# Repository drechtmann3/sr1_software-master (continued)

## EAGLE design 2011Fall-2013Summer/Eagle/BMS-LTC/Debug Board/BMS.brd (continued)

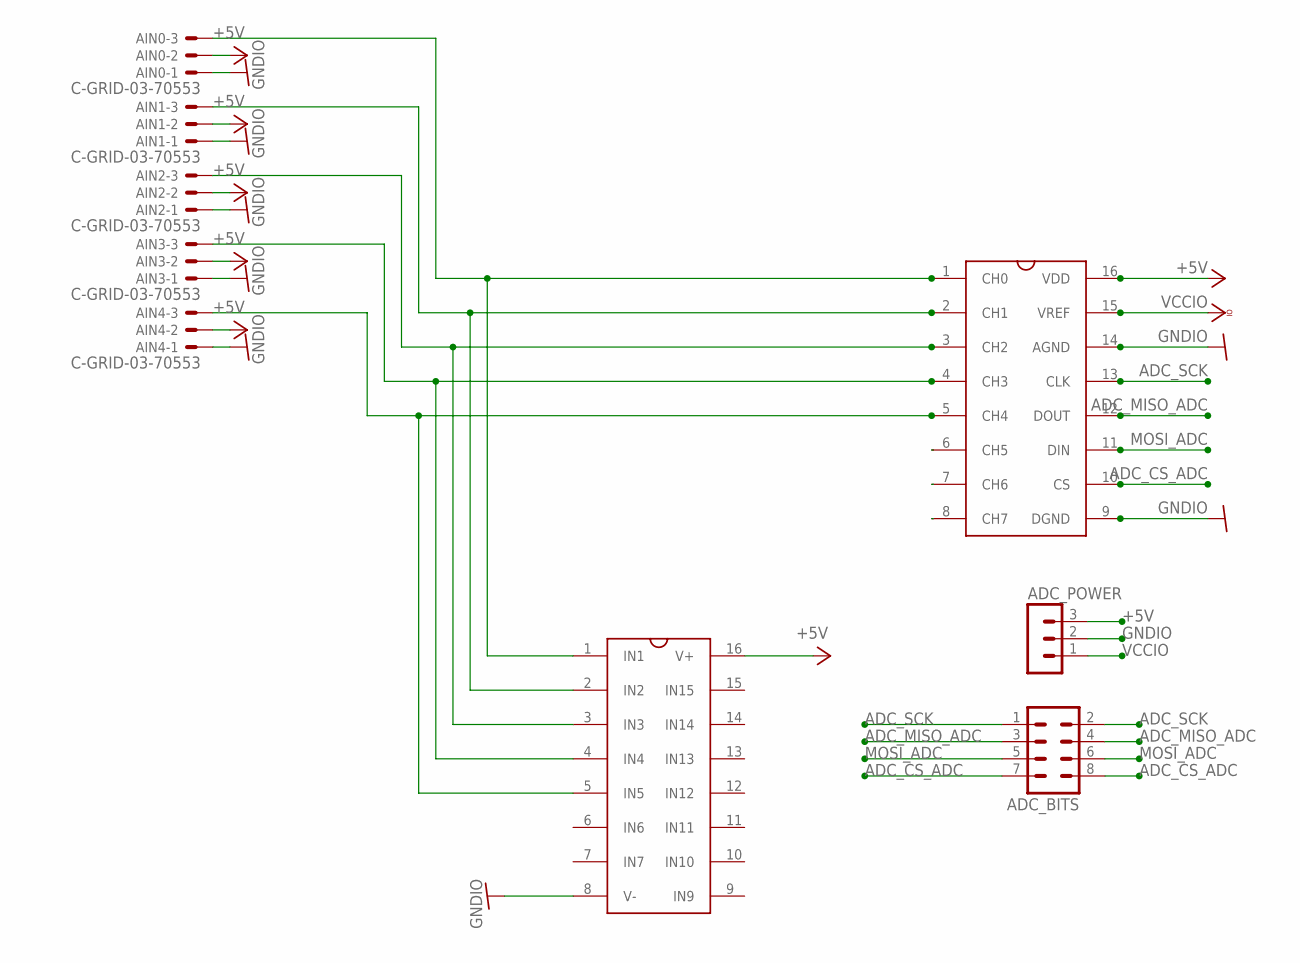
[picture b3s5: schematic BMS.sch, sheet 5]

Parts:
ADC_BITS: MA04-2
ADC_POWER: MA03-1
AIN0, AIN1, AIN2, AIN3, AIN4: C-GRID-03-70553; 70553-03
U$1: SP720APP; SO16
U$6: MCP-3008; SO16

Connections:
+5V: ADC_POWER.3, AIN0.2, AIN1.2, AIN2.2, AIN3.2, AIN4.2, U$1.16 (V+), U$6.16 (VDD); also elsewhere on the board
ADC_CS_ADC: ADC_BITS.7, ADC_BITS.8, U$6.10 (CS)
ADC_MISO_ADC: ADC_BITS.3, ADC_BITS.4, U$6.12 (DOUT)
ADC_SCK: ADC_BITS.1, ADC_BITS.2, U$6.13 (CLK)
GNDIO: ADC_POWER.2, AIN0.1, AIN1.1, AIN2.1, AIN3.1, AIN4.1, U$1.8 (V-), U$6.9 (DGND), U$6.14 (AGND); also elsewhere on the board
MOSI_ADC: ADC_BITS.5, ADC_BITS.6, U$6.11 (DIN)
unnamed: AIN0.3, U$1.1 (IN1), U$6.1 (CH0)
unnamed: AIN1.3, U$1.2 (IN2), U$6.2 (CH1)
unnamed: AIN2.3, U$1.3 (IN3), U$6.3 (CH2)
unnamed: AIN3.3, U$1.4 (IN4), U$6.4 (CH3)
unnamed: AIN4.3, U$1.5 (IN5), U$6.5 (CH4)
VCCIO: ADC_POWER.1, U$6.15 (VREF); also elsewhere on the board

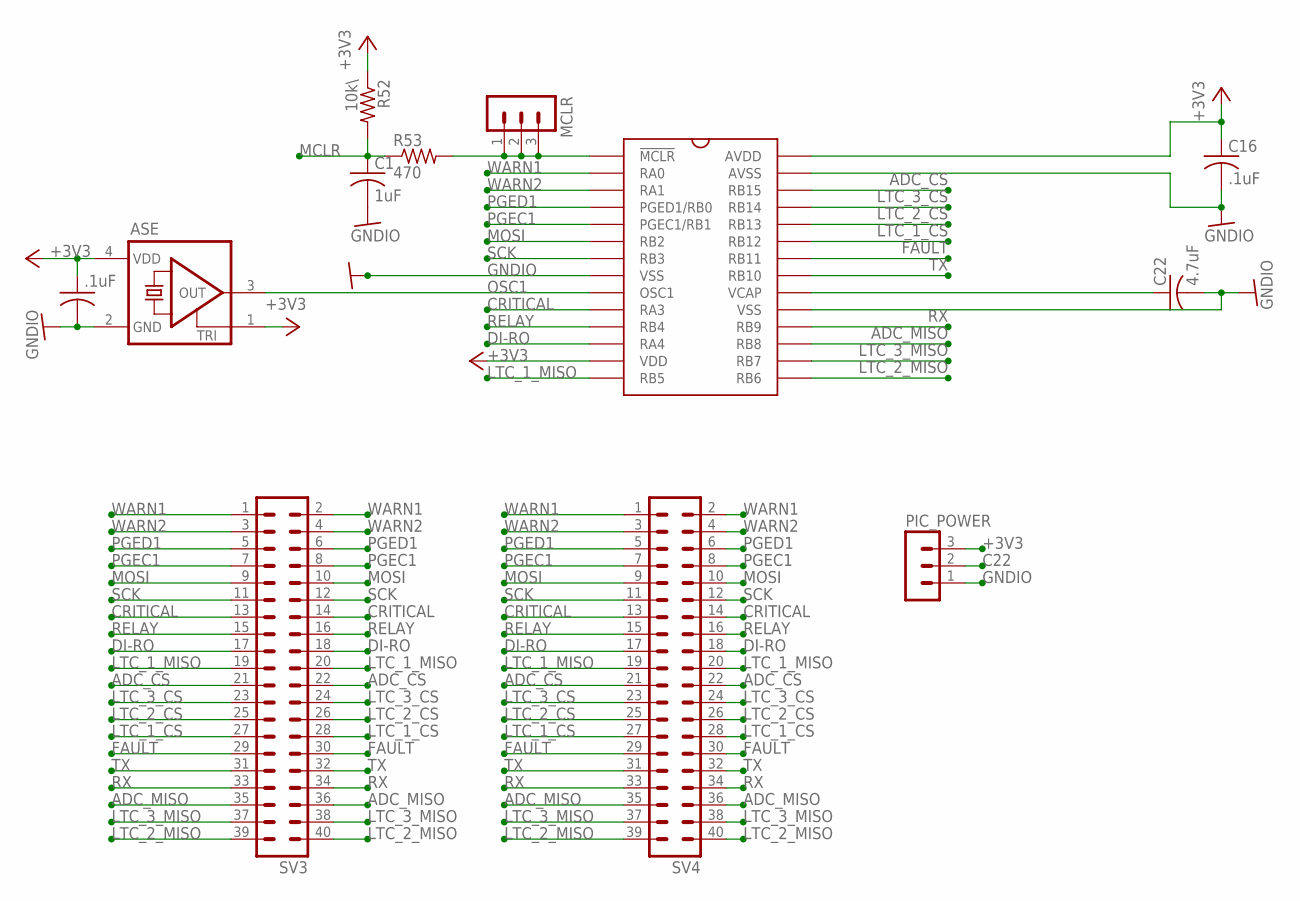
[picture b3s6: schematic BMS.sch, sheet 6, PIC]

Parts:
C1: 1uF; C1206
C16, C48: .1uF; C1206
C22: 4.7uF; C1206
MCLR: MA03-1
PIC_POWER: MA03-1
R52: 10k\; R1206
R53: 470; R1206
SV3, SV4: MA20-2
U$2: PIC24HJ128GP-202; SO28W
U$3: ASE

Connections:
+3V3: C16.1, C48.1, PIC_POWER.3, R52.1, U$2.13 (VDD), U$2.28 (AVDD), U$3.1 (TRI), U$3.4 (VDD); also elsewhere on the board
ADC_CS: SV3.21, SV3.22, SV4.21, SV4.22, U$2.26 (RB15)
ADC_MISO: SV3.35, SV3.36, SV4.35, SV4.36, U$2.17 (RB8)
C22: C22.1, PIC_POWER.2, U$2.20 (VCAP)
CRITICAL: SV3.13, SV3.14, SV4.13, SV4.14, U$2.10 (RA3)
DI-RO: SV3.17, SV3.18, SV4.17, SV4.18, U$2.12 (RA4)
FAULT: SV3.29, SV3.30, SV4.29, SV4.30, U$2.22 (RB11)
GNDIO: C1.2, C16.2, C22.2, C48.2, PIC_POWER.1, U$2.8 (VSS), U$2.19 (VSS), U$2.27 (AVSS), U$3.2 (GND); also elsewhere on the board
LTC_1_CS: SV3.27, SV3.28, SV4.27, SV4.28, U$2.23 (RB12)
LTC_1_MISO: SV3.19, SV3.20, SV4.19, SV4.20, U$2.14 (RB5)
LTC_2_CS: SV3.25, SV3.26, SV4.25, SV4.26, U$2.24 (RB13)
LTC_2_MISO: SV3.39, SV3.40, SV4.39, SV4.40, U$2.15 (RB6)
LTC_3_CS: SV3.23, SV3.24, SV4.23, SV4.24, U$2.25 (RB14)
LTC_3_MISO: SV3.37, SV3.38, SV4.37, SV4.38, U$2.16 (RB7)
MCLR: C1.1, R52.2, R53.1; also elsewhere on the board
MOSI: SV3.9, SV3.10, SV4.9, SV4.10, U$2.6 (RB2)
unnamed: MCLR.1, MCLR.2, MCLR.3, R53.2, U$2.1 (!MCLR!)
OSC1: U$2.9 (OSC1), U$3.3 (OUT); also elsewhere on the board
PGEC1: SV3.7, SV3.8, SV4.7, SV4.8, U$2.5 (PGEC1/RB1); also elsewhere on the board
PGED1: SV3.5, SV3.6, SV4.5, SV4.6, U$2.4 (PGED1/RB0); also elsewhere on the board
RELAY: SV3.15, SV3.16, SV4.15, SV4.16, U$2.11 (RB4)
RX: SV3.33, SV3.34, SV4.33, SV4.34, U$2.18 (RB9)
SCK: SV3.11, SV3.12, SV4.11, SV4.12, U$2.7 (RB3)
TX: SV3.31, SV3.32, SV4.31, SV4.32, U$2.21 (RB10)
WARN1: SV3.1, SV3.2, SV4.1, SV4.2, U$2.2 (RA0)
WARN2: SV3.3, SV3.4, SV4.3, SV4.4, U$2.3 (RA1)

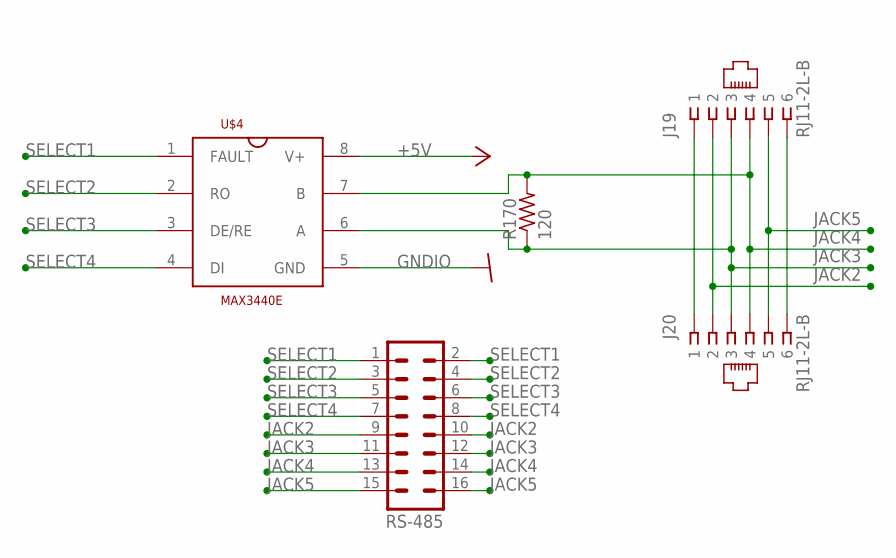
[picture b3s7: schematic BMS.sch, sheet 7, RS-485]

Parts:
J19, J20: RJ11-2L-B; RJ11-NO_SHIELD
R170: 120; R1206
RS-485: MA08-2
U$4: MAX3440E; SO-08

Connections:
+5V: U$4.8 (V+); also elsewhere on the board
GNDIO: U$4.5 (GND); also elsewhere on the board
JACK2: J19.2, J20.2, RS-485.9, RS-485.10
JACK3: J19.3, J20.3, R170.1, RS-485.11, RS-485.12, U$4.6 (A)
JACK4: J19.4, J20.4, R170.2, RS-485.13, RS-485.14, U$4.7 (B)
JACK5: J19.5, J20.5, RS-485.15, RS-485.16
unnamed: J19.1, J20.1
unnamed: J19.6, J20.6
SELECT1: RS-485.1, RS-485.2, U$4.1 (FAULT)
SELECT2: RS-485.3, RS-485.4, U$4.2 (RO)
SELECT3: RS-485.5, RS-485.6, U$4.3 (DE/RE)
SELECT4: RS-485.7, RS-485.8, U$4.4 (DI)

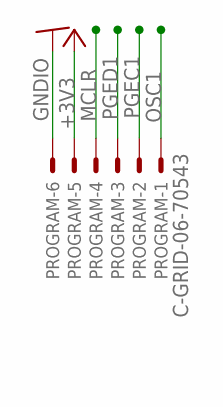
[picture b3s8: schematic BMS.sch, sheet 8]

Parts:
PROGRAM: C-GRID-06-70543; 70543-06

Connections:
+3V3: PROGRAM.5; also elsewhere on the board
GNDIO: PROGRAM.6; also elsewhere on the board
MCLR: PROGRAM.4; also elsewhere on the board
OSC1: PROGRAM.1; also elsewhere on the board
PGEC1: PROGRAM.2; also elsewhere on the board
PGED1: PROGRAM.3; also elsewhere on the board

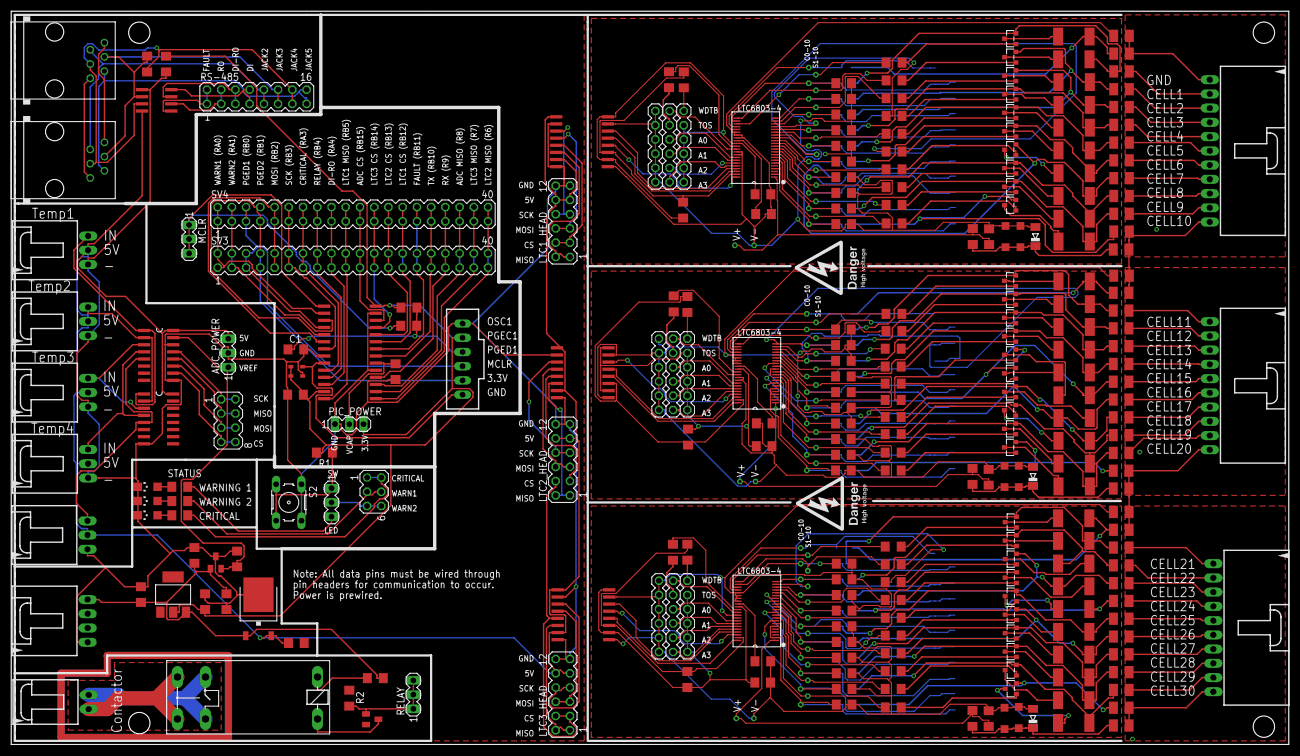
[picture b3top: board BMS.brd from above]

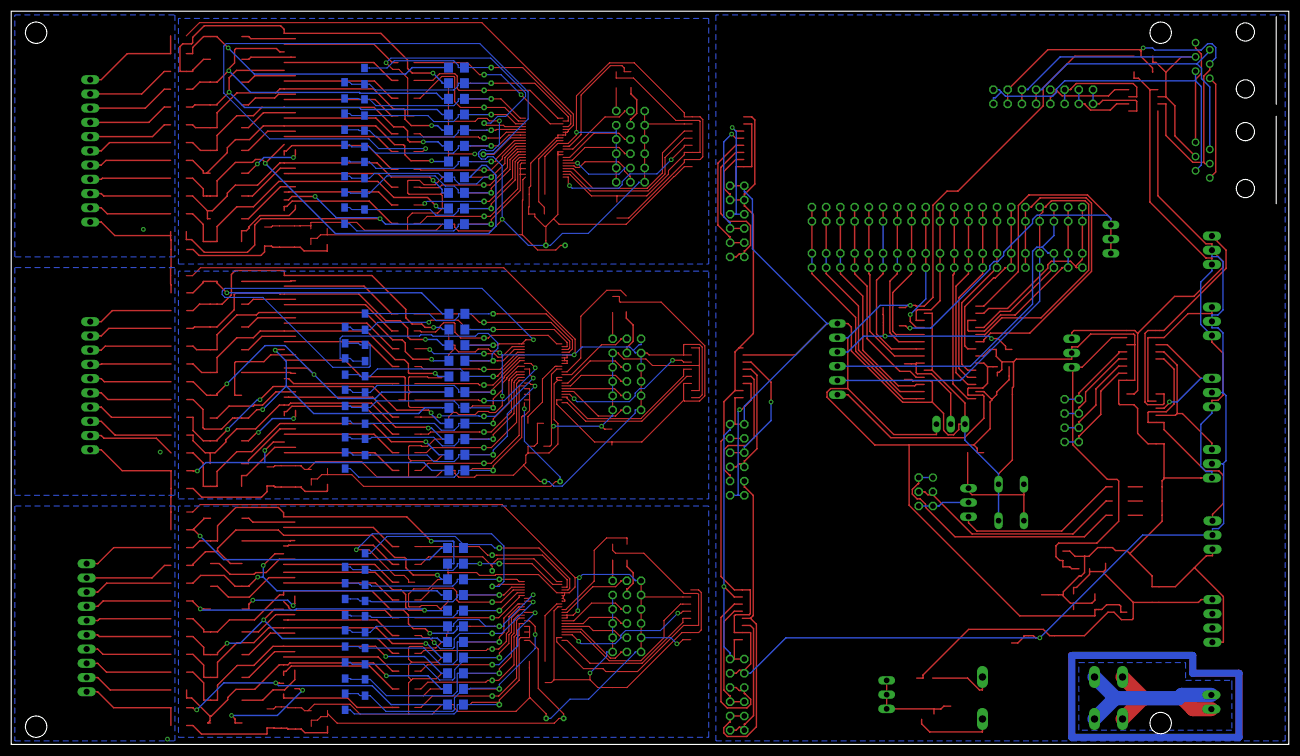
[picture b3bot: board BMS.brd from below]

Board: 2 copper layers, 228.0 x 130.8 mm, 389 parts (84 on the bottom side), 311 nets.

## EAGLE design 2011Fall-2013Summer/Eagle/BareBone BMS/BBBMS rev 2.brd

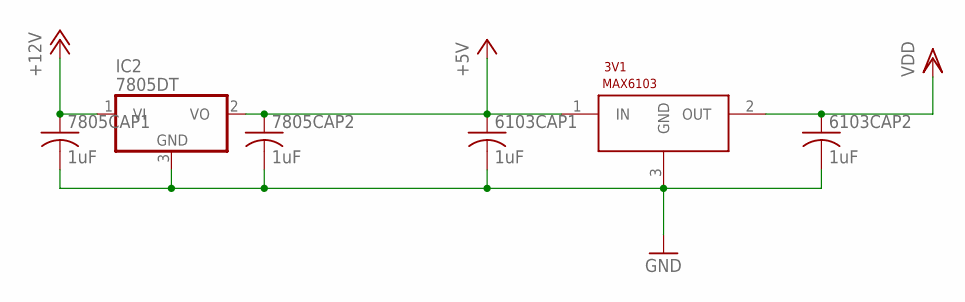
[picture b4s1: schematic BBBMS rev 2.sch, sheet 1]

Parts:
3V1: MAX6103; SOT23
6103CAP1, 6103CAP2, 7805CAP1, 7805CAP2: 1uF; C1206
IC2: 7805DT; TO252

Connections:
5V: 3V1.1 (IN), 6103CAP1.1, 7805CAP2.1, IC2.2 (VO); also elsewhere on the board
12V: 7805CAP1.1, IC2.1 (VI); also elsewhere on the board
GND: 3V1.3 (GND), 6103CAP1.2, 6103CAP2.2, 7805CAP1.2, 7805CAP2.2, IC2.3 (GND); also elsewhere on the board
VREF: 3V1.2 (OUT), 6103CAP2.1; also elsewhere on the board

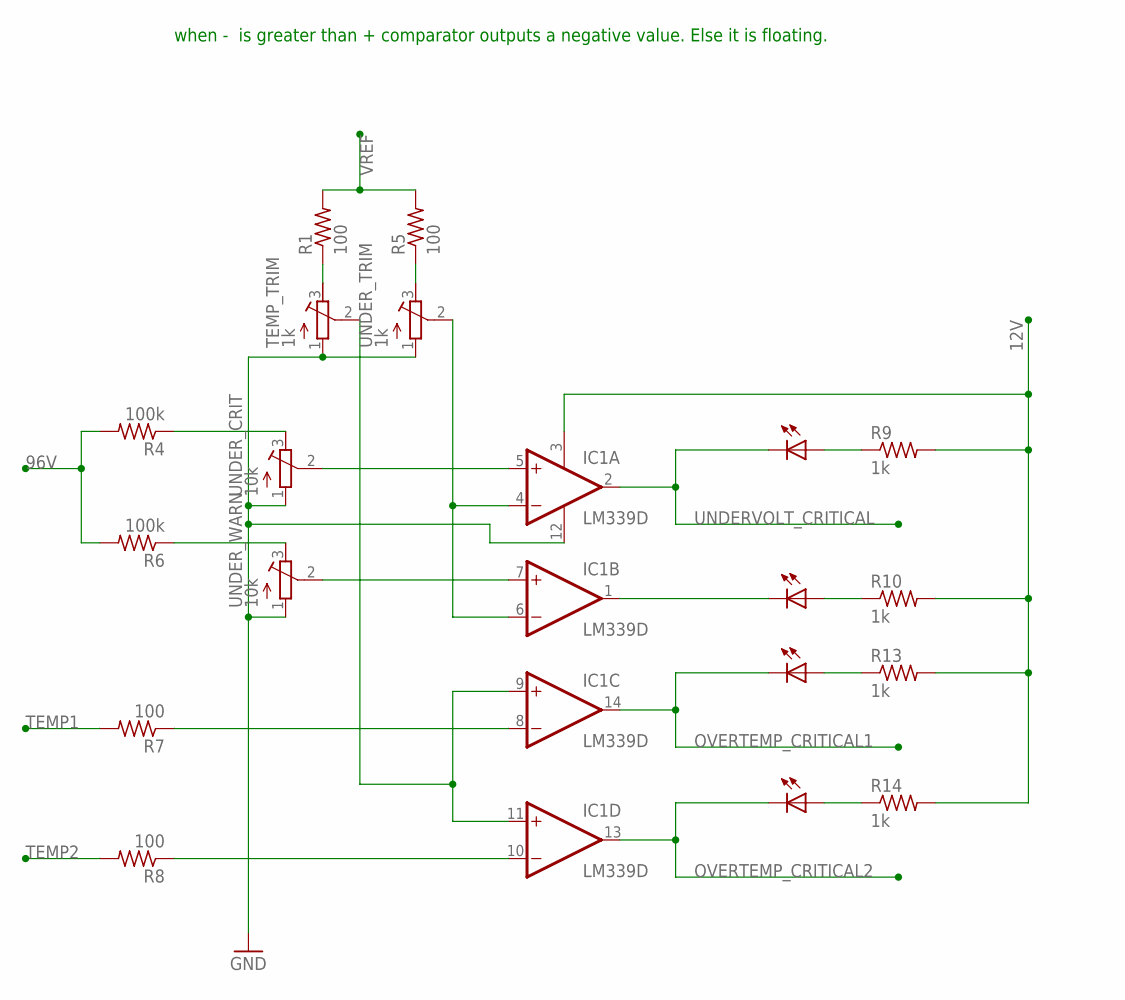
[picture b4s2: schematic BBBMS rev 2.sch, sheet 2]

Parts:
IC1: LM339D; SO14
OVERTEMP1, OVERTEMP2: LEDCHIPLED_1206; CHIPLED_1206
R1, R5, R7, R8: 100; R1206
R4, R6: 100k; R1206
R9, R10, R13, R14: 1k; R1206
TEMP_TRIM: 1k; RTRIMTS63Y
UNDERVOLT: LEDCHIPLED_1206; CHIPLED_1206
UNDERVOLT_WARN: LEDCHIPLED_1206; CHIPLED_1206
UNDER_CRIT: 10k; RTRIMTS63Y
UNDER_TRIM: 1k; RTRIMTS63Y
UNDER_WARN: 10k; RTRIMTS63Y

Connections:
12V: IC1.3 (V+), R9.2, R10.2, R13.2, R14.2; also elsewhere on the board
96V: R4.2, R6.2; also elsewhere on the board
GND: IC1.12 (GND), TEMP_TRIM.1 (A), UNDER_CRIT.1 (A), UNDER_TRIM.1 (A), UNDER_WARN.1 (A); also elsewhere on the board
unnamed: IC1.8 (-IN), R7.1
unnamed: IC1.7 (+IN), UNDER_WARN.2 (S)
unnamed: IC1.5 (+IN), UNDER_CRIT.2 (S)
unnamed: IC1.9 (+IN), IC1.11 (+IN), TEMP_TRIM.2 (S)
unnamed: R6.1, UNDER_WARN.3 (E)
unnamed: IC1.10 (-IN), R8.1
unnamed: R4.1, UNDER_CRIT.3 (E)
unnamed: IC1.4 (-IN), IC1.6 (-IN), UNDER_TRIM.2 (S)
unnamed: R5.1, UNDER_TRIM.3 (E)
unnamed: R1.1, TEMP_TRIM.3 (E)
unnamed: R9.1, UNDERVOLT.A
unnamed: R10.1, UNDERVOLT_WARN.A
unnamed: OVERTEMP1.A, R13.1
unnamed: OVERTEMP2.A, R14.1
OVERTEMP_CRITICAL1: IC1.14 (OUT), OVERTEMP1.C; also elsewhere on the board
OVERTEMP_CRITICAL2: IC1.13 (OUT), OVERTEMP2.C; also elsewhere on the board
TEMP1: R7.2; also elsewhere on the board
TEMP2: R8.2; also elsewhere on the board
UNDERVOLT_CRITICAL: IC1.2 (OUT), UNDERVOLT.C; also elsewhere on the board
UNDERVOLT_WARNING: IC1.1 (OUT), UNDERVOLT_WARN.C
VREF: R1.2, R5.2; also elsewhere on the board

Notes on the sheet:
when - is greater than + comparator outputs a negative value. Else it is floating.

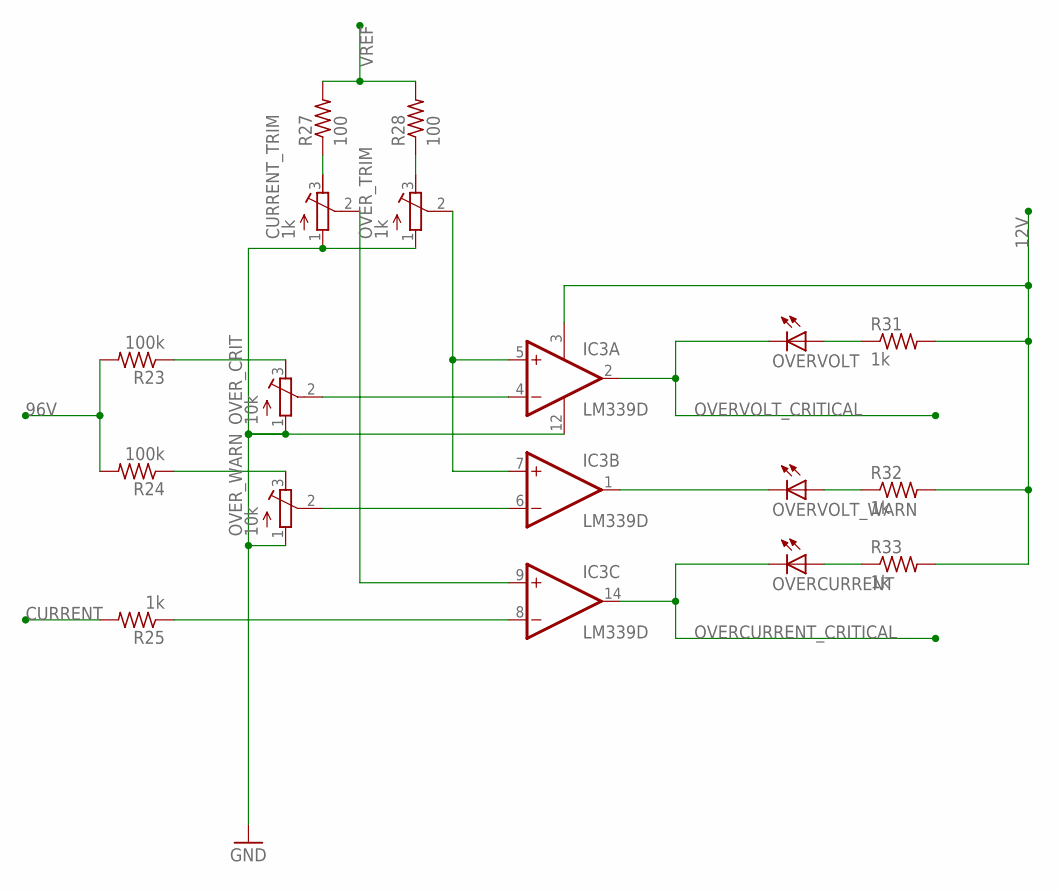
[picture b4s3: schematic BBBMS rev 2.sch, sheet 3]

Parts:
CURRENT_TRIM: 1k; RTRIMTS63Y
IC3: LM339D; SO14
OVERCURRENT: LEDCHIPLED_1206; CHIPLED_1206
OVERVOLT: LEDCHIPLED_1206; CHIPLED_1206
OVERVOLT_WARN: LEDCHIPLED_1206; CHIPLED_1206
OVER_CRIT: 10k; RTRIMTS63Y
OVER_TRIM: 1k; RTRIMTS63Y
OVER_WARN: 10k; RTRIMTS63Y
R23, R24: 100k; R1206
R25, R31, R32, R33: 1k; R1206
R27, R28: 100; R1206

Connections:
12V: IC3.3 (V+), R31.2, R32.2, R33.2; also elsewhere on the board
96V: R23.2, R24.2; also elsewhere on the board
CURRENT: R25.2; also elsewhere on the board
GND: CURRENT_TRIM.1 (A), IC3.12 (GND), OVER_CRIT.1 (A), OVER_TRIM.1 (A), OVER_WARN.1 (A); also elsewhere on the board
unnamed: IC3.6 (-IN), OVER_WARN.2 (S)
unnamed: IC3.4 (-IN), OVER_CRIT.2 (S)
unnamed: CURRENT_TRIM.2 (S), IC3.9 (+IN)
unnamed: OVER_CRIT.3 (E), R23.1
unnamed: OVER_WARN.3 (E), R24.1
unnamed: IC3.8 (-IN), R25.1
unnamed: IC3.5 (+IN), IC3.7 (+IN), OVER_TRIM.2 (S)
unnamed: OVER_TRIM.3 (E), R28.1
unnamed: CURRENT_TRIM.3 (E), R27.1
unnamed: OVERVOLT.A, R31.1
unnamed: OVERVOLT_WARN.A, R32.1
unnamed: OVERCURRENT.A, R33.1
OVERCURRENT_CRITICAL: IC3.14 (OUT), OVERCURRENT.C; also elsewhere on the board
OVERVOLT_CRITICAL: IC3.2 (OUT), OVERVOLT.C; also elsewhere on the board
OVERVOLT_WARNING1: IC3.1 (OUT), OVERVOLT_WARN.C
VREF: R27.2, R28.2; also elsewhere on the board

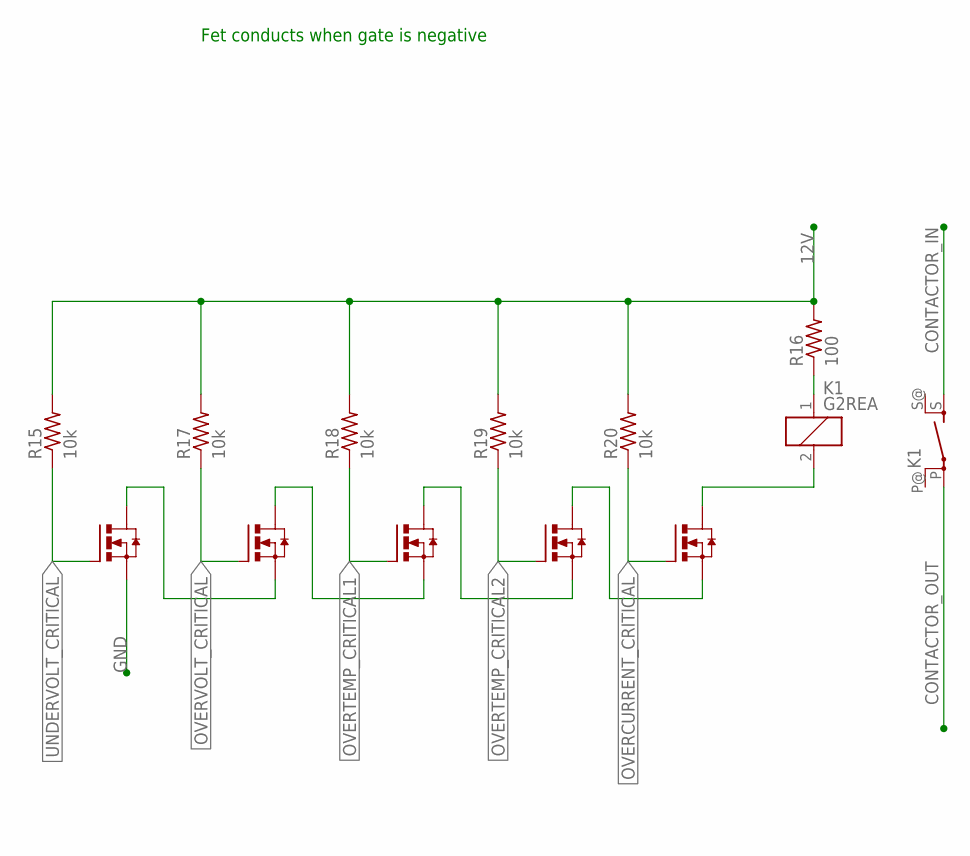
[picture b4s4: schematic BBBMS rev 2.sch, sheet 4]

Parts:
K1: G2REA
OVERCURRENT_FET: N-HEXFET-2D_SOT232-; SOT223
OVERTEMP1_FET, OVERTEMP2_FET: N-HEXFET-2D_SOT232-; SOT223
OVERVOLT_FET: N-HEXFET-2D_SOT232-; SOT223
R15, R17, R18, R19, R20: 10k; R1206
R16: 100; R1206
UNDERVOLT_FET: N-HEXFET-2D_SOT232-; SOT223

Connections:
12V: R15.2, R16.2, R17.2, R18.2, R19.2, R20.2; also elsewhere on the board
CONTACTOR_IN: K1.S; also elsewhere on the board
CONTACTOR_OUT: K1.P; also elsewhere on the board
GND: UNDERVOLT_FET.3 (S); also elsewhere on the board
unnamed: K1.2, OVERCURRENT_FET.2 (D), OVERCURRENT_FET.4 (D)
unnamed: OVERCURRENT_FET.3 (S), OVERTEMP2_FET.2 (D), OVERTEMP2_FET.4 (D)
unnamed: K1.1, R16.1
unnamed: OVERTEMP1_FET.2 (D), OVERTEMP1_FET.4 (D), OVERTEMP2_FET.3 (S)
unnamed: OVERTEMP1_FET.3 (S), OVERVOLT_FET.2 (D), OVERVOLT_FET.4 (D)
unnamed: OVERVOLT_FET.3 (S), UNDERVOLT_FET.2 (D), UNDERVOLT_FET.4 (D)
OVERCURRENT_CRITICAL: OVERCURRENT_FET.1 (G), R20.1; also elsewhere on the board
OVERTEMP_CRITICAL1: OVERTEMP1_FET.1 (G), R18.1; also elsewhere on the board
OVERTEMP_CRITICAL2: OVERTEMP2_FET.1 (G), R19.1; also elsewhere on the board
OVERVOLT_CRITICAL: OVERVOLT_FET.1 (G), R17.1; also elsewhere on the board
UNDERVOLT_CRITICAL: R15.1, UNDERVOLT_FET.1 (G); also elsewhere on the board

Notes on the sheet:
Fet conducts when gate is negative

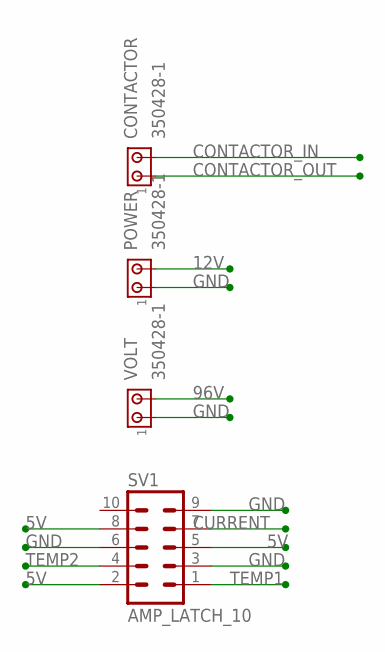
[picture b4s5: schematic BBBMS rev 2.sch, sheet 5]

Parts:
CONTACTOR: 350428-1
POWER: 350428-1
SV1: AMP_LATCH_10; MA05-2
VOLT: 350428-1

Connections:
5V: SV1.2, SV1.5, SV1.8; also elsewhere on the board
12V: POWER.2; also elsewhere on the board
96V: VOLT.2; also elsewhere on the board
CONTACTOR_IN: CONTACTOR.2; also elsewhere on the board
CONTACTOR_OUT: CONTACTOR.1; also elsewhere on the board
CURRENT: SV1.7; also elsewhere on the board
GND: POWER.1, SV1.3, SV1.6, SV1.9, VOLT.1; also elsewhere on the board
TEMP1: SV1.1; also elsewhere on the board
TEMP2: SV1.4; also elsewhere on the board

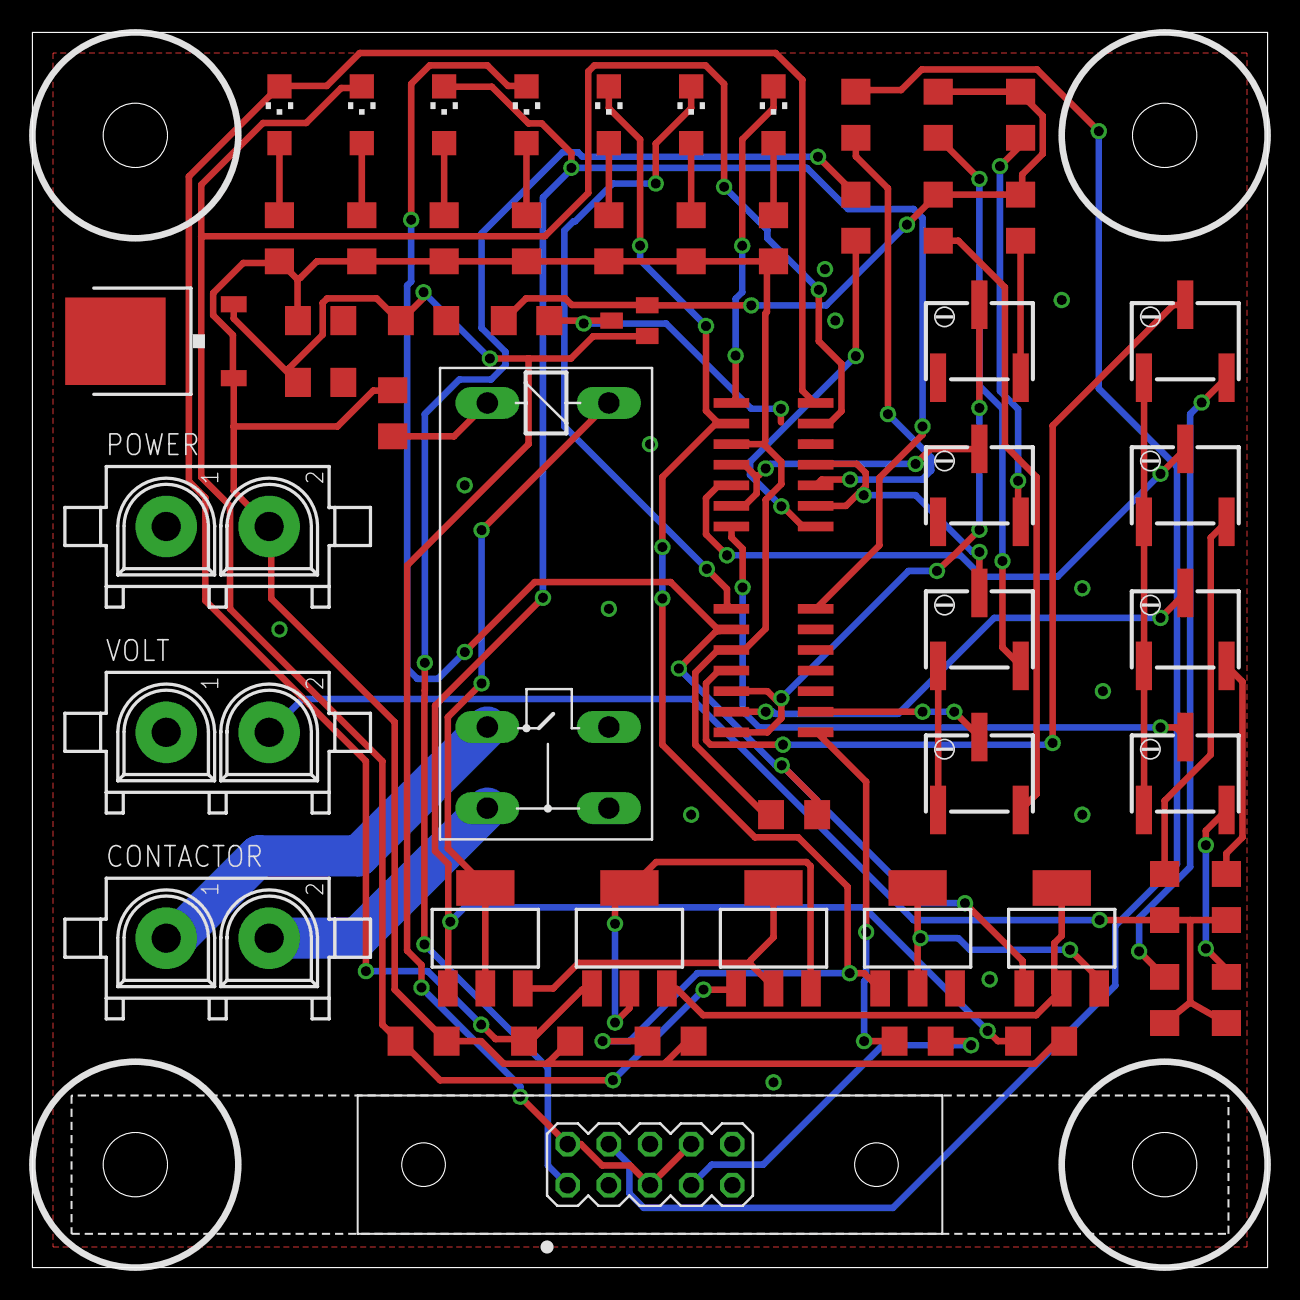
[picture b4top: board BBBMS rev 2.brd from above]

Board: 2 copper layers, 76.2 x 76.2 mm, 57 parts (0 on the bottom side), 49 nets.

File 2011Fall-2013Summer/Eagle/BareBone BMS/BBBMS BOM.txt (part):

Partlist exported from C:/Users/Reid Kersey/Documents/School/Solar Jackets/SubVersion/Eagle/BareBone BMS/BBBMS.sch at 11/14/2012 2:11:55 AM

Part            Value               Device              Package  Description                                                    MF                   MPN OC_FARNELL OC_NEWARK
3V1             MAX6103             MAX6103             SOT23                                                                                                                
6103CAP1        1uF                 C-USC0402           C0402    CAPACITOR, American symbol                                                                                  
6103CAP2        1uF                 C-USC0402           C0402    CAPACITOR, American symbol                                                                                  
7805CAP1        1uF                 C-USC0402           C0402    CAPACITOR, American symbol                                                                                  
7805CAP2        1uF                 C-USC0402           C0402    CAPACITOR, American symbol                                                                                  
CONTACTOR       350428-1            350428-1            350428-1 Universal MATE-N-LOK .250" Centerline, 600 V, 19 - 36 A max                                                 
CURRENT_TRIM    1k                  R-TRIMM64W          RTRIM64W Trimm resistor                                                                                              
IC1             LM339D              LM339D              SO14     Low Power Low Offset Voltage Quad Comparators                                                               
IC2             7805DT              7805DT              TO252    Positive VOLTAGE REGULATOR                                                                                  
IC3             LM339D              LM339D              SO14     Low Power Low Offset Voltage Quad Comparators                                                               
K1              G2REA               G2REA               G2REA    RELAY                                                                                   unknown    unknown  
OVERCURRENT     TLLG4400            TLLG4400            LED3MM   Low Current (2mA) LED 3 mm Tinted Diffused Package color GREEN VISHAY SEMICONDUCTOR     1612435             
OVERCURRENT_FET N-HEXFET-2D_SOT232- N-HEXFET-2D_SOT232- SOT223   HEXFET® Power MOSFET 2 Drain connects                                                                       
OVERTEMP1       TLLG4400            TLLG4400            LED3MM   Low Current (2mA) LED 3 mm Tinted Diffused Package color GREEN VISHAY SEMICONDUCTOR     1612435             
OVERTEMP1_FET   N-HEXFET-2D_SOT232- N-HEXFET-2D_SOT232- SOT223   HEXFET® Power MOSFET 2 Drain connects                                                                       
OVERTEMP2       TLLG4400            TLLG4400            LED3MM   Low Current (2mA) LED 3 mm Tinted Diffused Package color GREEN VISHAY SEMICONDUCTOR     1612435             
OVERTEMP2_FET   N-HEXFET-2D_SOT232- N-HEXFET-2D_SOT232- SOT223   HEXFET® Power MOSFET 2 Drain connects                                                                       
OVERVOLT        TLLG4400            TLLG4400            LED3MM   Low Current (2mA) LED 3 mm Tinted Diffused Package color GREEN VISHAY SEMICONDUCTOR     1612435             
OVERVOLT_FET    N-HEXFET-2D_SOT232- N-HEXFET-2D_SOT232- SOT223   HEXFET® Power MOSFET 2 Drain connects                                                                       
OVERVOLT_WARN   TLLG4400            TLLG4400            LED3MM   Low Current (2mA) LED 3 mm Tinted Diffused Package color GREEN VISHAY SEMICONDUCTOR     1612435             
OVER_CRIT       10k                 R-TRIMM64W          RTRIM64W Trimm resistor                                                                                              
OVER_TRIM       1k                  R-TRIMM64W          RTRIM64W Trimm resistor                                                                                              
OVER_WARN       10K                 R-TRIMM64W          RTRIM64W Trimm resistor                                                                                              
POWER           350428-1            350428-1            350428-1 Universal MATE-N-LOK .250" Centerline, 600 V, 19 - 36 A max                                                 
R1              100                 R-US_M1406          M1406    RESISTOR, American symbol                                                                                   
R4              100k                R-US_M1406          M1406    RESISTOR, American symbol                                                                                   
R5              100                 R-US_M1406          M1406    RESISTOR, American symbol                                                                                   
R6              100k                R-US_M1406          M1406    RESISTOR, American symbol                                                                                   
R7              100                 R-US_M1406          M1406    RESISTOR, American symbol                                                                                   
R8              100                 R-US_M1406          M1406    RESISTOR, American symbol                                                                                   
R9              1k                  R-US_M1406          M1406    RESISTOR, American symbol                                                                                   
R10             1k                  R-US_M1406          M1406    RESISTOR, American symbol                                                                                   
R13             1k                  R-US_M1406          M1406    RESISTOR, American symbol                                                                                   
R14             1k                  R-US_M1406          M1406    RESISTOR, American symbol                                                                                   
R15             1k                  R-US_M1406          M1406    RESISTOR, American symbol                                                                                   
R16             100                 R-US_M1406          M1406    RESISTOR, American symbol                                                                                   
R17             1k                  R-US_M1406          M1406    RESISTOR, American symbol                                                                                   
R18             1k                  R-US_M1406          M1406    RESISTOR, American symbol                                                                                   
R19             1k                  R-US_M1406          M1406    RESISTOR, American symbol                                                                                   
R20             1k                  R-US_M1406          M1406    RESISTOR, American symbol                                                                                   
R23             100k                R-US_M1406          M1406    RESISTOR, American symbol                                                                                   
R24             100k                R-US_M1406          M1406    RESISTOR, American symbol                                                                                   
R25             1k                  R-US_M1406          M1406    RESISTOR, American symbol                                                                                   
R27             100                 R-US_M1406          M1406    RESISTOR, American symbol                                                                                   
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
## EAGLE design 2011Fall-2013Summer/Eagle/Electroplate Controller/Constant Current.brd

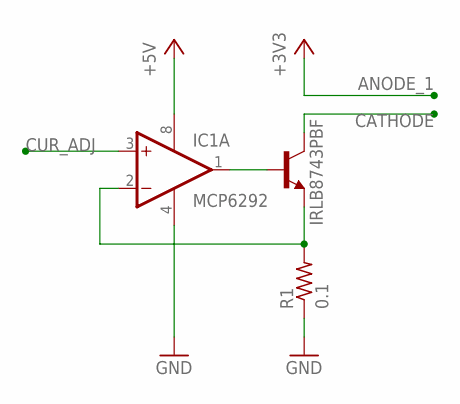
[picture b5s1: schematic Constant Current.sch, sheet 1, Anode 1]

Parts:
IC1: MCP6292; SO08
R1: 0.1; R1206
T1: IRLB8743PBF; TO220BV

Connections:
+5V: IC1.8 (V+); also elsewhere on the board
CATHODE: T1.2 (C); also elsewhere on the board
CUR_ADJ: IC1.3 (+IN); also elsewhere on the board
GND: IC1.4 (V-), R1.1; also elsewhere on the board
unnamed: IC1.2 (-IN), R1.2, T1.3 (E)
unnamed: IC1.1 (OUT), T1.1 (B)

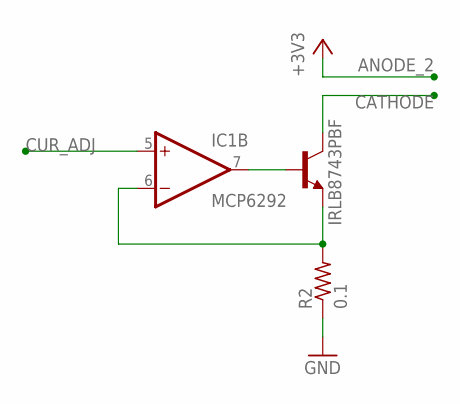
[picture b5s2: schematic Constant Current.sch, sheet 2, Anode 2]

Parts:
IC1: MCP6292; SO08
R2: 0.1; R1206
T2: IRLB8743PBF; TO220BV

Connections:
CATHODE: T2.2 (C); also elsewhere on the board
CUR_ADJ: IC1.5 (+IN); also elsewhere on the board
GND: R2.1; also elsewhere on the board
unnamed: IC1.6 (-IN), R2.2, T2.3 (E)
unnamed: IC1.7 (OUT), T2.1 (B)

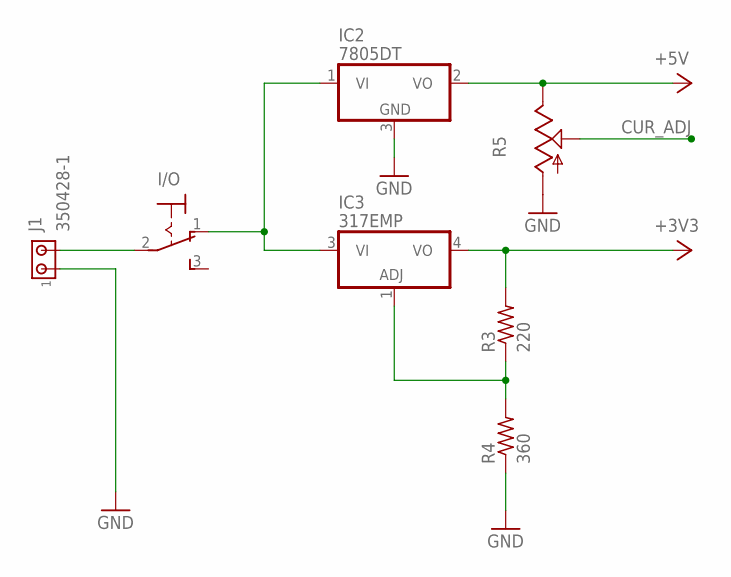
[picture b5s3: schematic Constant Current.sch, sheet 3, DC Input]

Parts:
I/O: M9040P
IC2: 7805DT; TO252
IC3: 317EMP; SOT223
J1: 350428-1
R3: 220; M1206
R4: 360; M1206
R5: TRIM_US-RJ9W; RJ9W

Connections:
+3V3: IC3.4 (VO), R3.2
+5V: IC2.2 (VO), R5.E; also elsewhere on the board
CUR_ADJ: R5.S; also elsewhere on the board
GND: IC2.3 (GND), J1.1, R4.1, R5.A; also elsewhere on the board
unnamed: I/O.2, J1.2
unnamed: IC3.1 (ADJ), R3.1, R4.2
unnamed: I/O.1 (O), IC2.1 (VI), IC3.3 (VI)

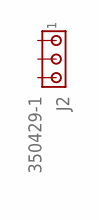
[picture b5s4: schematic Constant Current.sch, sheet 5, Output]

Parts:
J2: 350429-1

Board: 2 copper layers, 13 parts (0 on the bottom side), 12 nets, no tracks yet.

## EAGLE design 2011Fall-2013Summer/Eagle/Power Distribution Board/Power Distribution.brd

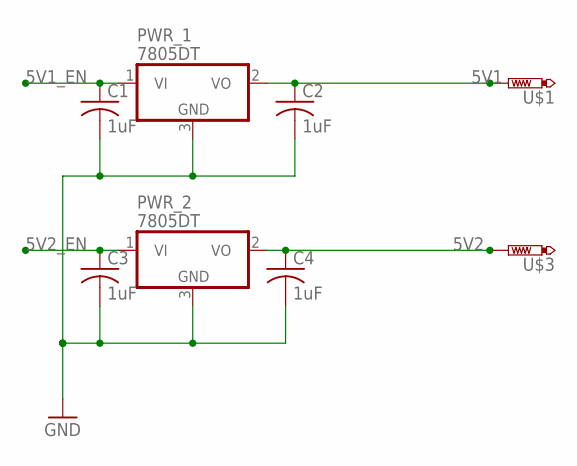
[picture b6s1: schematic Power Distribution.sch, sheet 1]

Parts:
C1, C2, C3, C4: 1uF; C1206
PWR_1, PWR_2: 7805DT; TO252
U$1, U$3: TESTPAD-20MIL; 20MIL

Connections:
5V1: C2.1, PWR_1.2 (VO), U$1.P$1; also elsewhere on the board
5V1_EN: C1.1, PWR_1.1 (VI); also elsewhere on the board
5V2: C4.1, PWR_2.2 (VO), U$3.P$1; also elsewhere on the board
5V2_EN: C3.1, PWR_2.1 (VI); also elsewhere on the board
GND: C1.2, C2.2, C3.2, C4.2, PWR_1.3 (GND), PWR_2.3 (GND); also elsewhere on the board
